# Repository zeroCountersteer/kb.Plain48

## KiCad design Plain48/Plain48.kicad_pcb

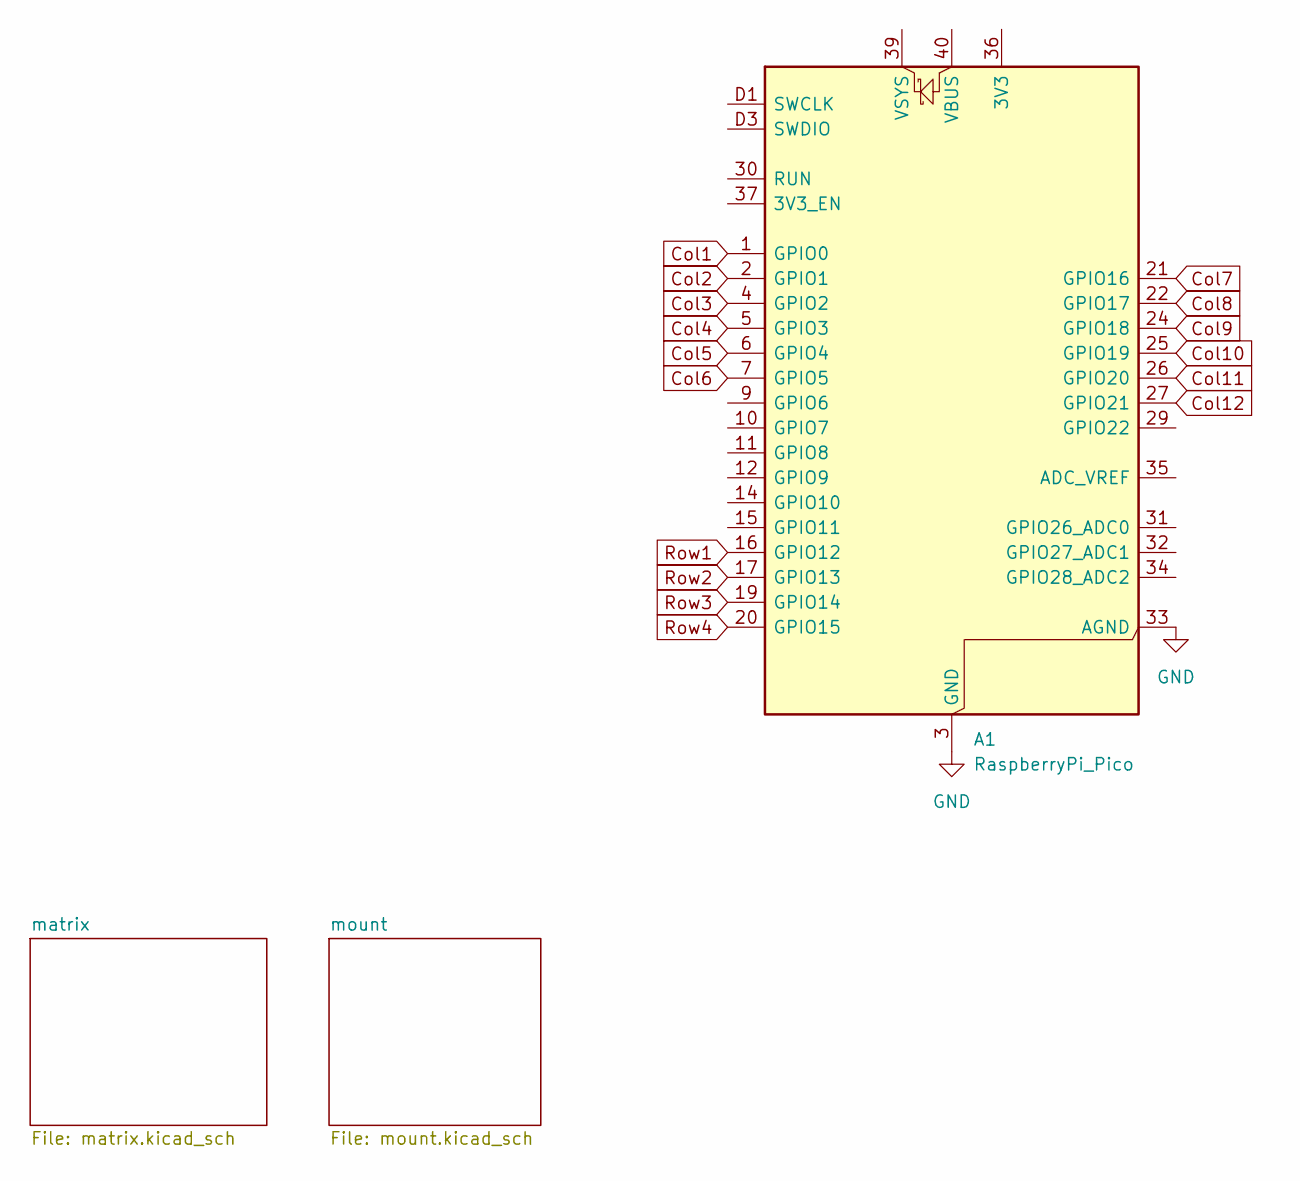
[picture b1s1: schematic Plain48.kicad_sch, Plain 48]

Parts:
A1: RaspberryPi_Pico; RaspberryPi_Pico_SMD_HandSolder

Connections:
Col1: A1.1 (GPIO0); also elsewhere on the board
Col2: A1.2 (GPIO1); also elsewhere on the board
Col3: A1.4 (GPIO2); also elsewhere on the board
Col4: A1.5 (GPIO3); also elsewhere on the board
Col5: A1.6 (GPIO4); also elsewhere on the board
Col6: A1.7 (GPIO5); also elsewhere on the board
Col7: A1.21 (GPIO16); also elsewhere on the board
Col8: A1.22 (GPIO17); also elsewhere on the board
Col9: A1.24 (GPIO18); also elsewhere on the board
Col10: A1.25 (GPIO19); also elsewhere on the board
Col11: A1.26 (GPIO20); also elsewhere on the board
Col12: A1.27 (GPIO21); also elsewhere on the board
GND: A1.3 (GND), A1.8 (GND), A1.13 (GND), A1.18 (GND), A1.23 (GND), A1.28 (GND), A1.33 (AGND), A1.38 (GND), A1.D2 (GND); also elsewhere on the board
Row1: A1.16 (GPIO12); also elsewhere on the board
Row2: A1.17 (GPIO13); also elsewhere on the board
Row3: A1.19 (GPIO14); also elsewhere on the board
Row4: A1.20 (GPIO15); also elsewhere on the board

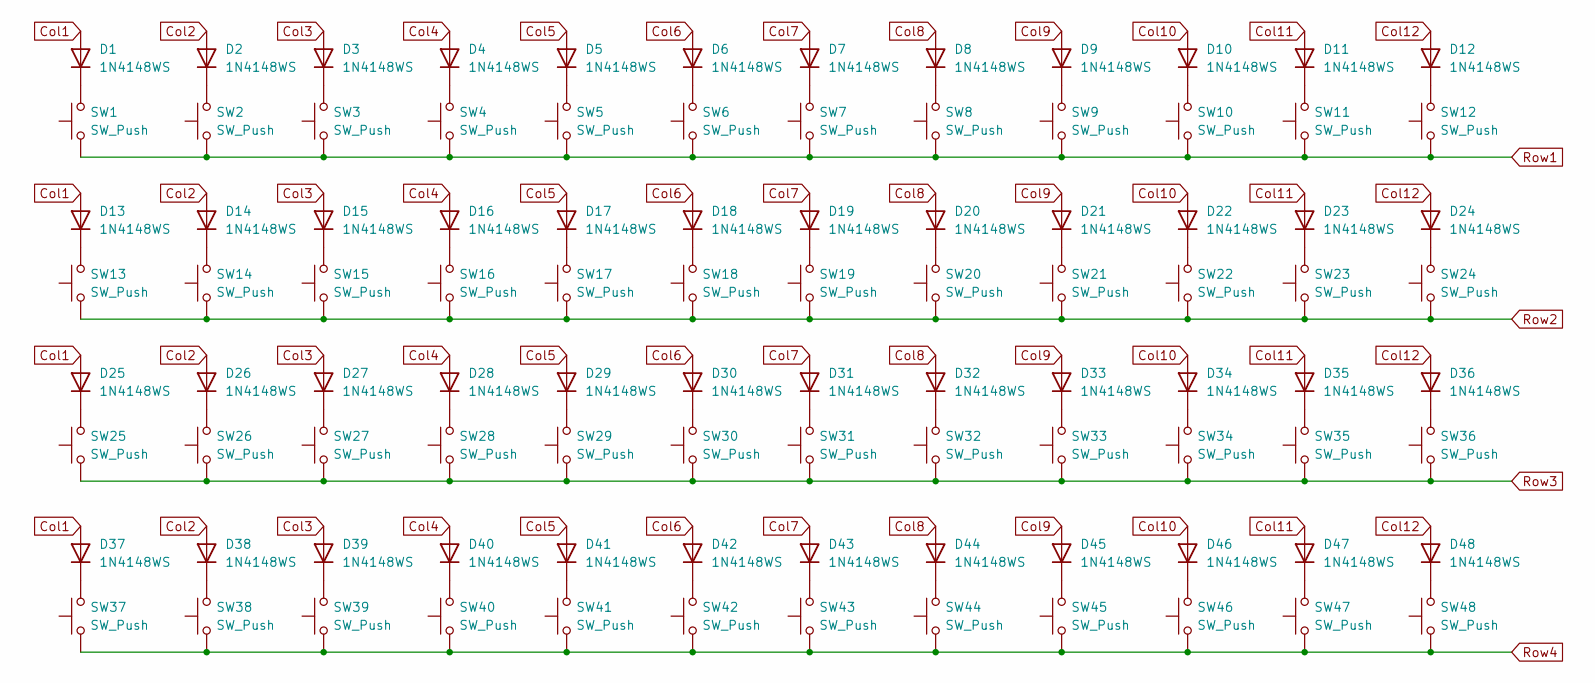
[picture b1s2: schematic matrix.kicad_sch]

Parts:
D1, D2, D3, D4, D5, D6, D7, D8, D9, D10, D11, D12, D13, D14, D15, D16, D17, D18, D19, D20, D21, D22, D23, D24, D25, D26, D27, D28, D29, D30, D31, D32, D33, D34, D35, D36, D37, D38, D39, D40, D41, D42, D43, D44, D45, D46, D47, D48: 1N4148WS; D_SOD-323_HandSoldering
SW1, SW2, SW3, SW4, SW5, SW6, SW7, SW8, SW9, SW10, SW11, SW12, SW13, SW14, SW15, SW16, SW17, SW18, SW19, SW20, SW21, SW22, SW23, SW24, SW25, SW26, SW27, SW28, SW29, SW30, SW31, SW32, SW33, SW34, SW35, SW36, SW37, SW38, SW39, SW40, SW41, SW42, SW43, SW44, SW45, SW46, SW47, SW48: SW_Push; SW_Kailh_Choc_V2

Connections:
Col1: D1.2 (A), D13.2 (A), D25.2 (A), D37.2 (A); also elsewhere on the board
Col2: D2.2 (A), D14.2 (A), D26.2 (A), D38.2 (A); also elsewhere on the board
Col3: D3.2 (A), D15.2 (A), D27.2 (A), D39.2 (A); also elsewhere on the board
Col4: D4.2 (A), D16.2 (A), D28.2 (A), D40.2 (A); also elsewhere on the board
Col5: D5.2 (A), D17.2 (A), D29.2 (A), D41.2 (A); also elsewhere on the board
Col6: D6.2 (A), D18.2 (A), D30.2 (A), D42.2 (A); also elsewhere on the board
Col7: D7.2 (A), D19.2 (A), D31.2 (A), D43.2 (A); also elsewhere on the board
Col8: D8.2 (A), D20.2 (A), D32.2 (A), D44.2 (A); also elsewhere on the board
Col9: D9.2 (A), D21.2 (A), D33.2 (A), D45.2 (A); also elsewhere on the board
Col10: D10.2 (A), D22.2 (A), D34.2 (A), D46.2 (A); also elsewhere on the board
Col11: D11.2 (A), D23.2 (A), D35.2 (A), D47.2 (A); also elsewhere on the board
Col12: D12.2 (A), D24.2 (A), D36.2 (A), D48.2 (A); also elsewhere on the board
unnamed: D1.1 (K), SW1.2
unnamed: D2.1 (K), SW2.2
unnamed: D3.1 (K), SW3.2
unnamed: D4.1 (K), SW4.2
unnamed: D5.1 (K), SW5.2
unnamed: D6.1 (K), SW6.2
unnamed: D7.1 (K), SW7.2
unnamed: D8.1 (K), SW8.2
unnamed: D9.1 (K), SW9.2
unnamed: D10.1 (K), SW10.2
unnamed: D11.1 (K), SW11.2
unnamed: D12.1 (K), SW12.2
unnamed: D13.1 (K), SW13.2
unnamed: D14.1 (K), SW14.2
unnamed: D15.1 (K), SW15.2
unnamed: D16.1 (K), SW16.2
unnamed: D17.1 (K), SW17.2
unnamed: D18.1 (K), SW18.2
unnamed: D19.1 (K), SW19.2
unnamed: D20.1 (K), SW20.2
unnamed: D21.1 (K), SW21.2
unnamed: D22.1 (K), SW22.2
unnamed: D23.1 (K), SW23.2
unnamed: D24.1 (K), SW24.2
unnamed: D25.1 (K), SW25.2
unnamed: D26.1 (K), SW26.2
unnamed: D27.1 (K), SW27.2
unnamed: D28.1 (K), SW28.2
unnamed: D29.1 (K), SW29.2
unnamed: D30.1 (K), SW30.2
unnamed: D31.1 (K), SW31.2
unnamed: D32.1 (K), SW32.2
unnamed: D33.1 (K), SW33.2
unnamed: D34.1 (K), SW34.2
unnamed: D35.1 (K), SW35.2
unnamed: D36.1 (K), SW36.2
unnamed: D37.1 (K), SW37.2
unnamed: D38.1 (K), SW38.2
unnamed: D39.1 (K), SW39.2
unnamed: D40.1 (K), SW40.2
unnamed: D41.1 (K), SW41.2
unnamed: D42.1 (K), SW42.2
unnamed: D43.1 (K), SW43.2
unnamed: D44.1 (K), SW44.2
unnamed: D45.1 (K), SW45.2
unnamed: D46.1 (K), SW46.2
unnamed: D47.1 (K), SW47.2
unnamed: D48.1 (K), SW48.2
Row1: SW1.1, SW2.1, SW3.1, SW4.1, SW5.1, SW6.1, SW7.1, SW8.1, SW9.1, SW10.1, SW11.1, SW12.1; also elsewhere on the board
Row2: SW13.1, SW14.1, SW15.1, SW16.1, SW17.1, SW18.1, SW19.1, SW20.1, SW21.1, SW22.1, SW23.1, SW24.1; also elsewhere on the board
Row3: SW25.1, SW26.1, SW27.1, SW28.1, SW29.1, SW30.1, SW31.1, SW32.1, SW33.1, SW34.1, SW35.1, SW36.1; also elsewhere on the board
Row4: SW37.1, SW38.1, SW39.1, SW40.1, SW41.1, SW42.1, SW43.1, SW44.1, SW45.1, SW46.1, SW47.1, SW48.1; also elsewhere on the board

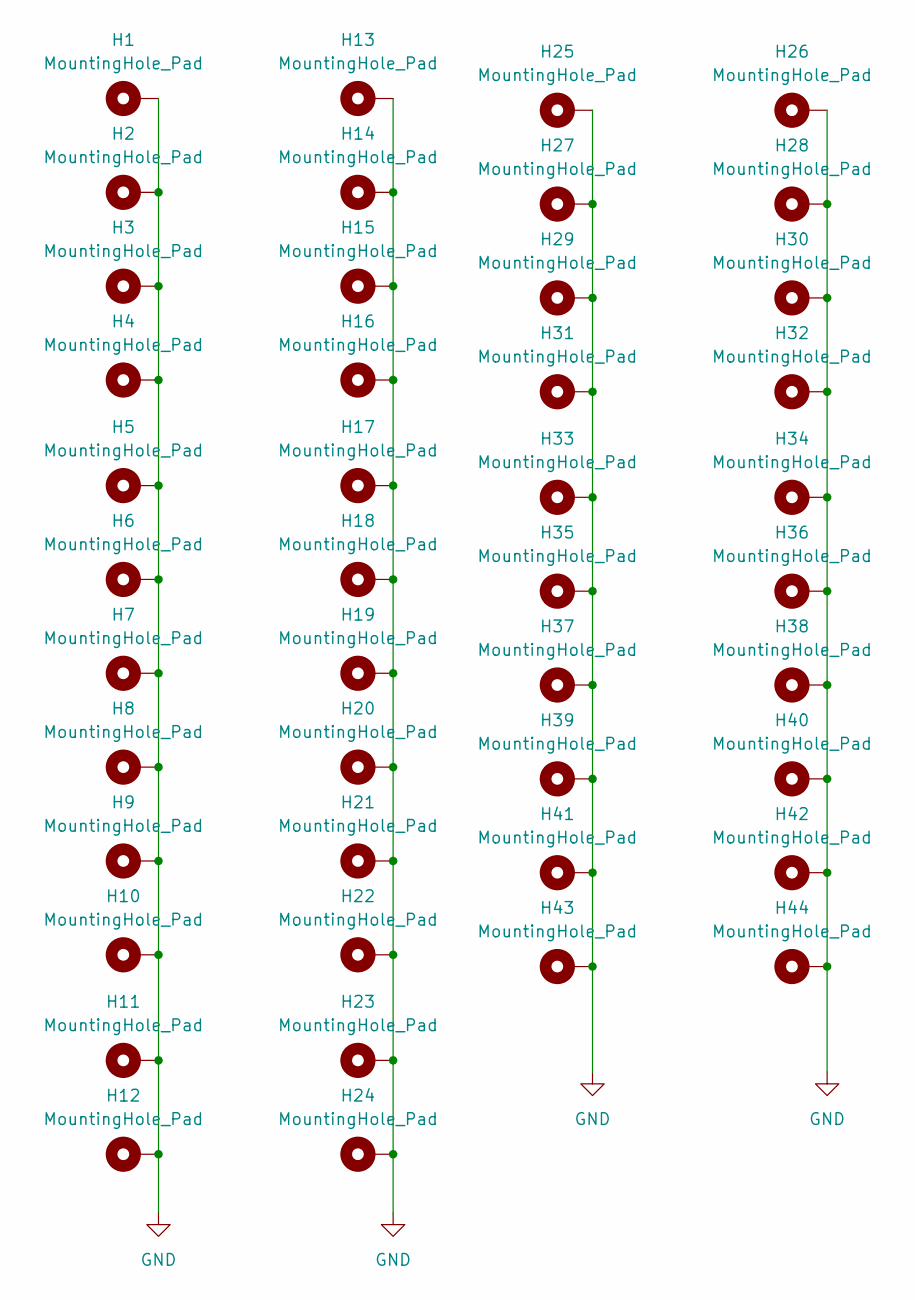
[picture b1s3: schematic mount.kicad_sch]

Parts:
H1, H2, H3, H4, H5, H6, H7, H8, H9, H10, H11, H12, H13, H14, H15, H16, H17, H18, H19, H20, H21, H22, H23, H24, H25, H26, H27, H28, H29, H30, H31, H32, H33, H34, H35, H36, H37, H38, H39, H40, H41, H42, H43, H44: MountingHole_Pad; MountingHole_2.2mm_M2_DIN965_Pad

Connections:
GND: H1.1, H2.1, H3.1, H4.1, H5.1, H6.1, H7.1, H8.1, H9.1, H10.1, H11.1, H12.1, H13.1, H14.1, H15.1, H16.1, H17.1, H18.1, H19.1, H20.1, H21.1, H22.1, H23.1, H24.1, H25.1, H26.1, H27.1, H28.1, H29.1, H30.1, H31.1, H32.1, H33.1, H34.1, H35.1, H36.1, H37.1, H38.1, H39.1, H40.1, H41.1, H42.1, H43.1, H44.1; also elsewhere on the board

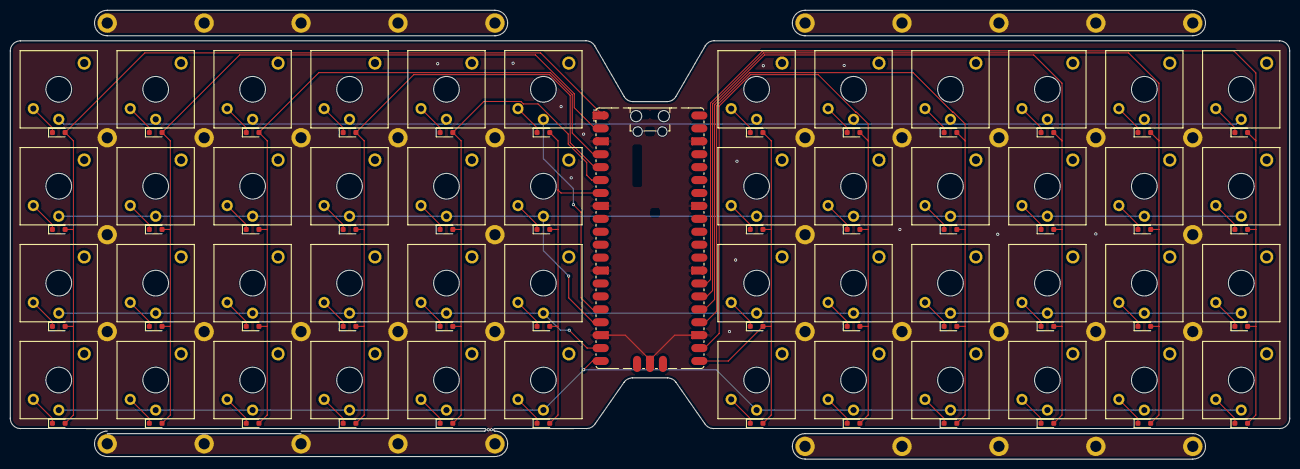
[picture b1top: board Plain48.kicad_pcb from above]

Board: 2 copper layers, 251.5 x 88.2 mm, 141 parts (0 on the bottom side), 65 nets.
